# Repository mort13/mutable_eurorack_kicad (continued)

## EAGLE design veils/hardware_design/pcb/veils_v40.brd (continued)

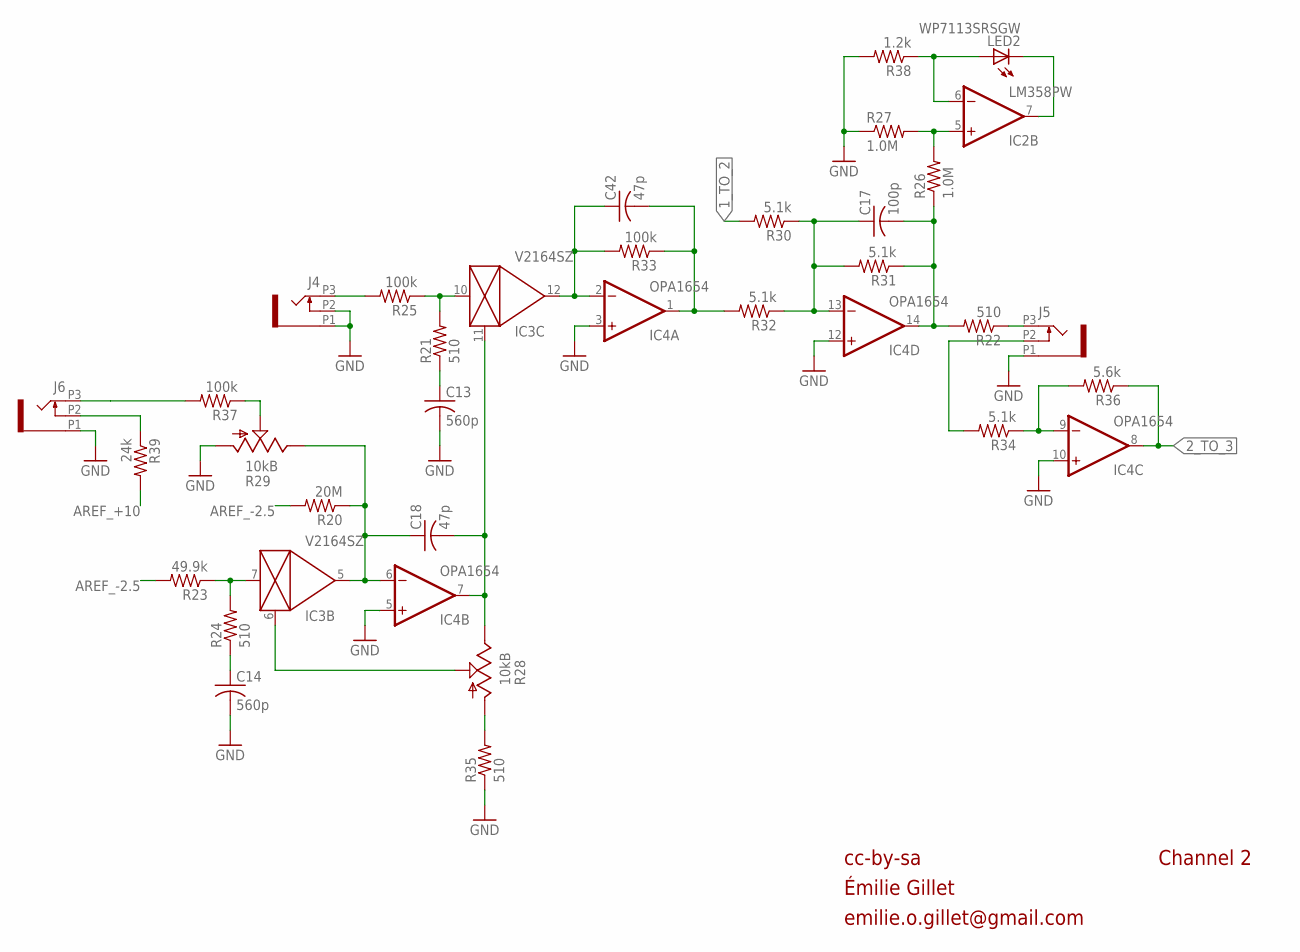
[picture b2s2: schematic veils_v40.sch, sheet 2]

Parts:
C13, C14: 560p; C0402
C17: 100p; C0402
C18, C42: 47p; C0402
IC2: LM358PW; TSSOP8
IC3: V2164SZ; SOIC16N
IC4: OPA1654; TSSOP14
J4, J5, J6: PJ301_THONKICONN6; WQP_PJ_301M6
LED2: WP7113SRSGW; LED5MM
R20: 20M; R0402
R21, R22, R24, R35: 510; R0402
R23: 49.9k; R0402
R25, R33, R37: 100k; R0402
R26, R27: 1.0M; R0402
R28: 10kB; ALPS_POT_VERTICAL
R29: 10kB; ALPS_POT_VERTICAL_PS
R30, R31, R32, R34: 5.1k; R0402
R36: 5.6k; R0402
R38: 1.2k; R0402
R39: 24k; R0402

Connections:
1_TO_2: R30.2; also elsewhere on the board
2_TO_3: IC4.8 (OUT), R36.1; also elsewhere on the board
AREF_+10: R39.2; also elsewhere on the board
AREF_-2.5: R20.2, R23.2; also elsewhere on the board
FOO1: IC3.7 (IN), R23.1, R24.2
GND: C13.2, C14.2, IC4.3 (+IN), IC4.5 (+IN), IC4.10 (+IN), IC4.12 (+IN), J4.P1 (1), J4.P2 (2), J5.P1 (1), J6.P1 (1), R27.1, R29.P$3 (A), R35.1, R38.2; also elsewhere on the board
unnamed: J4.P3 (3), R25.2
unnamed: IC2.5 (+IN), R26.2, R27.2
unnamed: J5.P3 (3), R22.1
unnamed: C13.1, R21.1
unnamed: IC3.10 (IN), R21.2, R25.1
unnamed: IC3.6 (CTRL), R28.P$2 (S)
unnamed: C17.1, IC4.13 (-IN), R30.1, R31.2, R32.1
unnamed: C18.2, IC3.11 (CTRL), IC4.7 (OUT), R28.P$1 (E)
unnamed: R28.P$3 (A), R35.2
unnamed: IC2.7 (OUT), LED2.K (C)
unnamed: IC2.6 (-IN), LED2.A, R38.1
unnamed: IC4.9 (-IN), R34.1, R36.2
unnamed: J5.P2 (2), R34.2
unnamed: C42.2, IC4.1 (OUT), R32.2, R33.1
unnamed: R29.P$2 (S), R37.1
unnamed: C14.1, R24.1
unnamed: C18.1, IC3.5 (OUT), IC4.6 (-IN), R20.1, R29.P$1 (E)
unnamed: J6.P3 (3), R37.2
unnamed: C42.1, IC3.12 (OUT), IC4.2 (-IN), R33.2
unnamed: J6.P2 (2), R39.1
OUT2: C17.2, IC4.14 (OUT), R22.2, R26.1, R31.1

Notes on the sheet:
cc-by-sa
Channel 2
Émilie Gillet
emilie.o.gillet@gmail.com

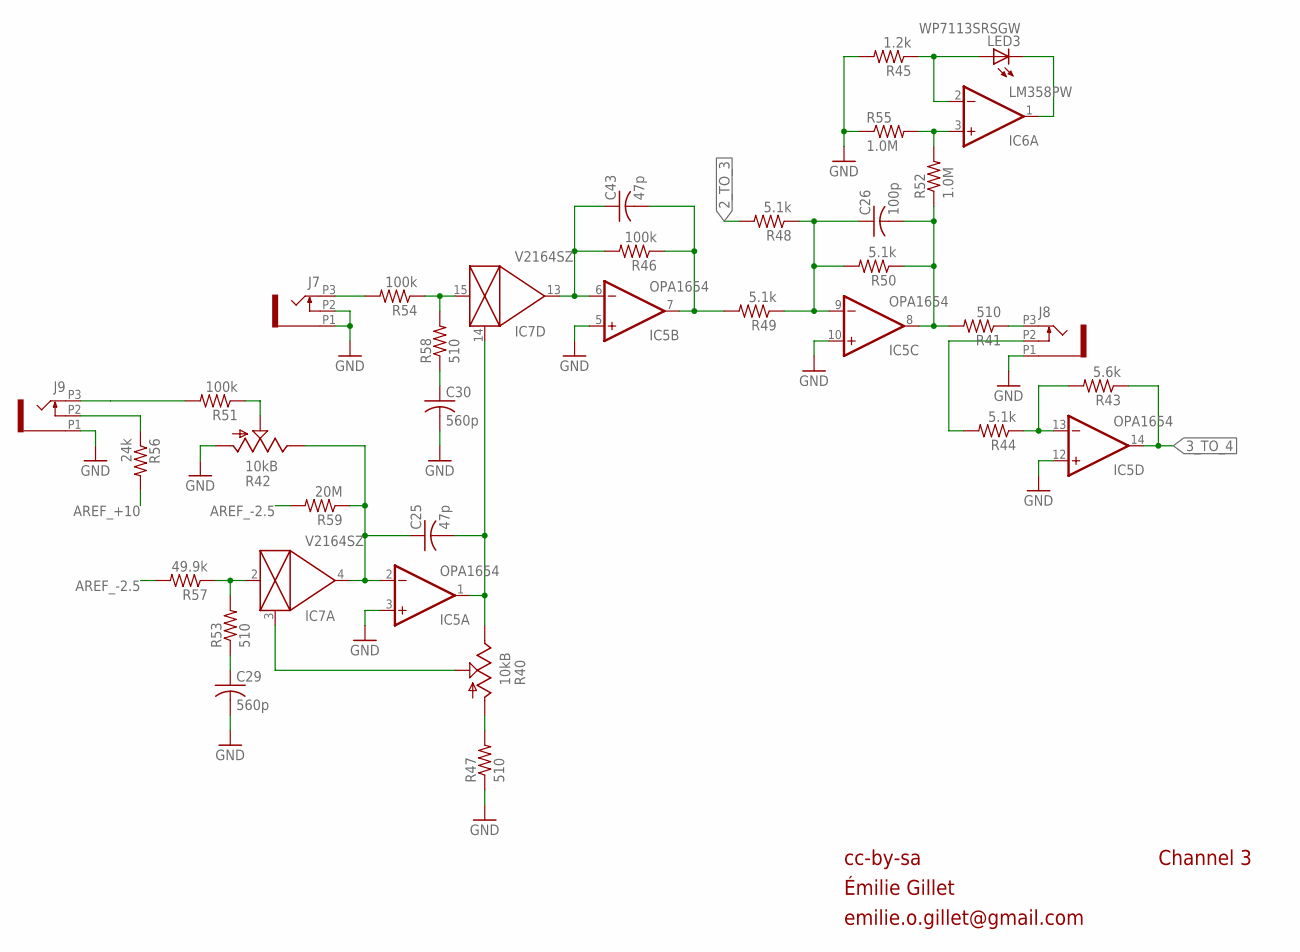
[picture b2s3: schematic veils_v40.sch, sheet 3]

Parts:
C25, C43: 47p; C0402
C26: 100p; C0402
C29, C30: 560p; C0402
IC5: OPA1654; TSSOP14
IC6: LM358PW; TSSOP8
IC7: V2164SZ; SOIC16N
J7, J8, J9: PJ301_THONKICONN6; WQP_PJ_301M6
LED3: WP7113SRSGW; LED5MM
R40: 10kB; ALPS_POT_VERTICAL
R41, R47, R53, R58: 510; R0402
R42: 10kB; ALPS_POT_VERTICAL_PS
R43: 5.6k; R0402
R44, R48, R49, R50: 5.1k; R0402
R45: 1.2k; R0402
R46, R51, R54: 100k; R0402
R52, R55: 1.0M; R0402
R56: 24k; R0402
R57: 49.9k; R0402
R59: 20M; R0402

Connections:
2_TO_3: R48.2; also elsewhere on the board
3_TO_4: IC5.14 (OUT), R43.1; also elsewhere on the board
AREF_+10: R56.2; also elsewhere on the board
AREF_-2.5: R57.2, R59.2; also elsewhere on the board
FOO2: IC7.2 (IN), R53.2, R57.1
GND: C29.2, C30.2, IC5.3 (+IN), IC5.5 (+IN), IC5.10 (+IN), IC5.12 (+IN), J7.P1 (1), J7.P2 (2), J8.P1 (1), J9.P1 (1), R42.P$3 (A), R45.2, R47.1, R55.1; also elsewhere on the board
unnamed: IC6.3 (+IN), R52.2, R55.2
unnamed: J8.P3 (3), R41.1
unnamed: IC7.3 (CTRL), R40.P$2 (S)
unnamed: C25.2, IC5.1 (OUT), IC7.14 (CTRL), R40.P$1 (E)
unnamed: R40.P$3 (A), R47.2
unnamed: C30.1, R58.1
unnamed: IC7.15 (IN), R54.1, R58.2
unnamed: C26.1, IC5.9 (-IN), R48.1, R49.1, R50.2
unnamed: J9.P2 (2), R56.1
unnamed: J7.P3 (3), R54.2
unnamed: J9.P3 (3), R51.2
unnamed: C43.1, IC5.6 (-IN), IC7.13 (OUT), R46.2
unnamed: IC6.1 (OUT), LED3.K (C)
unnamed: IC6.2 (-IN), LED3.A, R45.1
unnamed: IC5.13 (-IN), R43.2, R44.1
unnamed: J8.P2 (2), R44.2
unnamed: C29.1, R53.1
unnamed: C25.1, IC5.2 (-IN), IC7.4 (OUT), R42.P$1 (E), R59.1
unnamed: R42.P$2 (S), R51.1
unnamed: C43.2, IC5.7 (OUT), R46.1, R49.2
OUT3: C26.2, IC5.8 (OUT), R41.2, R50.1, R52.1

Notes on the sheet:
cc-by-sa
Channel 3
Émilie Gillet
emilie.o.gillet@gmail.com

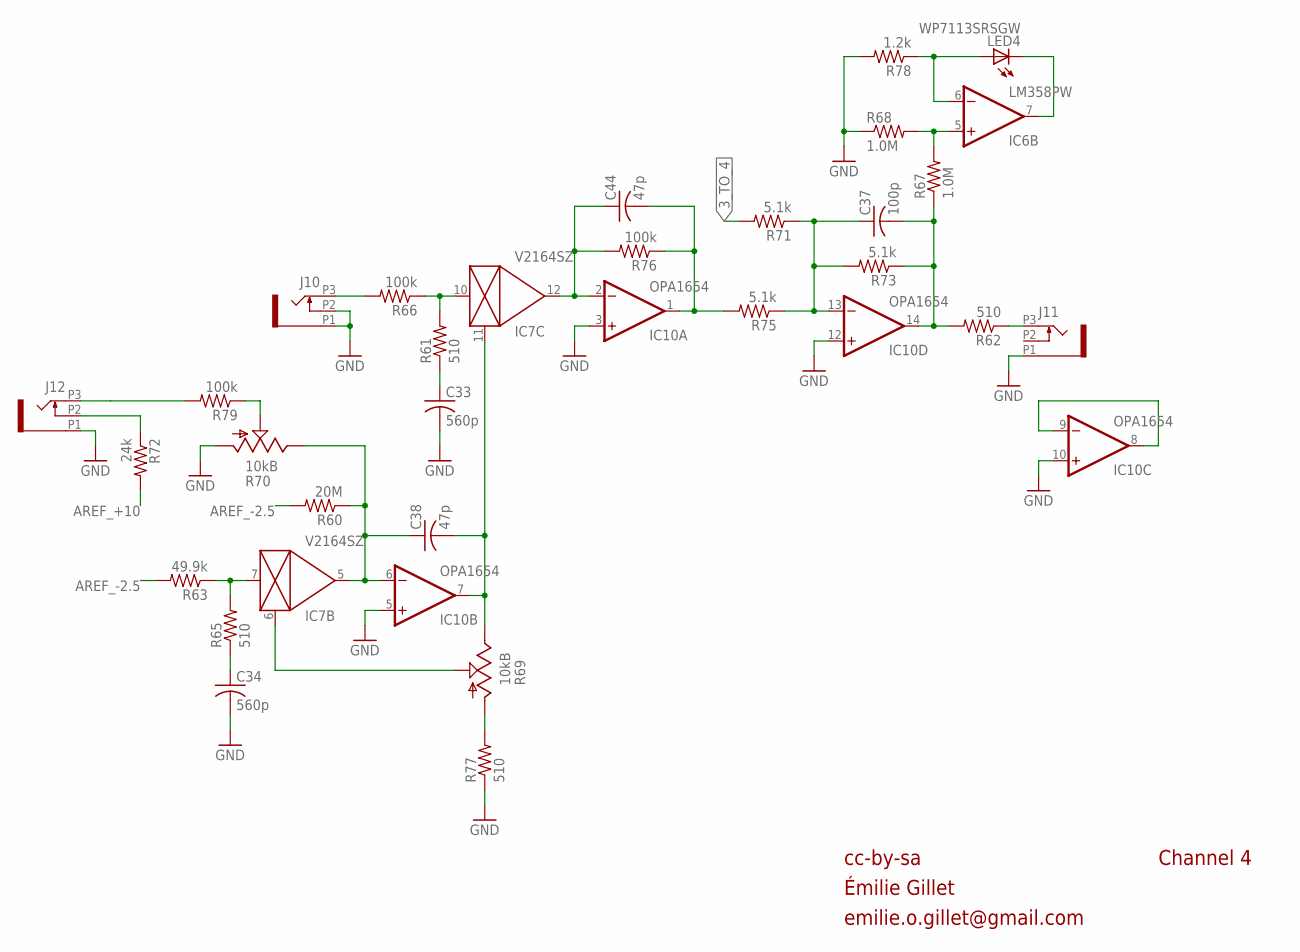
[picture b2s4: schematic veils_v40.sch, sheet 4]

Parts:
C33, C34: 560p; C0402
C37: 100p; C0402
C38, C44: 47p; C0402
IC6: LM358PW; TSSOP8
IC7: V2164SZ; SOIC16N
IC10: OPA1654; TSSOP14
J10, J11, J12: PJ301_THONKICONN6; WQP_PJ_301M6
LED4: WP7113SRSGW; LED5MM
R60: 20M; R0402
R61, R62, R65, R77: 510; R0402
R63: 49.9k; R0402
R66, R76, R79: 100k; R0402
R67, R68: 1.0M; R0402
R69: 10kB; ALPS_POT_VERTICAL
R70: 10kB; ALPS_POT_VERTICAL_PS
R71, R73, R75: 5.1k; R0402
R72: 24k; R0402
R78: 1.2k; R0402

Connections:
3_TO_4: R71.2; also elsewhere on the board
AREF_+10: R72.2; also elsewhere on the board
AREF_-2.5: R60.2, R63.2; also elsewhere on the board
FOO3: IC7.7 (IN), R63.1, R65.2
GND: C33.2, C34.2, IC10.3 (+IN), IC10.5 (+IN), IC10.10 (+IN), IC10.12 (+IN), J10.P1 (1), J10.P2 (2), J11.P1 (1), J12.P1 (1), R68.1, R70.P$3 (A), R77.1, R78.2; also elsewhere on the board
unnamed: IC10.8 (OUT), IC10.9 (-IN)
unnamed: IC6.5 (+IN), R67.2, R68.2
unnamed: C38.2, IC7.11 (CTRL), IC10.7 (OUT), R69.P$1 (E)
unnamed: IC7.6 (CTRL), R69.P$2 (S)
unnamed: R69.P$3 (A), R77.2
unnamed: C44.1, IC7.12 (OUT), IC10.2 (-IN), R76.2
unnamed: J10.P3 (3), R66.2
unnamed: J11.P3 (3), R62.1
unnamed: C33.1, R61.1
unnamed: IC7.10 (IN), R61.2, R66.1
unnamed: C37.1, IC10.13 (-IN), R71.1, R73.2, R75.1
unnamed: J12.P3 (3), R79.2
unnamed: IC6.7 (OUT), LED4.K (C)
unnamed: IC6.6 (-IN), LED4.A, R78.1
unnamed: C44.2, IC10.1 (OUT), R75.2, R76.1
unnamed: R70.P$2 (S), R79.1
unnamed: C34.1, R65.1
unnamed: C38.1, IC7.5 (OUT), IC10.6 (-IN), R60.1, R70.P$1 (E)
unnamed: J12.P2 (2), R72.1
OUT4: C37.2, IC10.14 (OUT), R62.2, R67.1, R73.1

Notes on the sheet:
cc-by-sa
Channel 4
Émilie Gillet
emilie.o.gillet@gmail.com

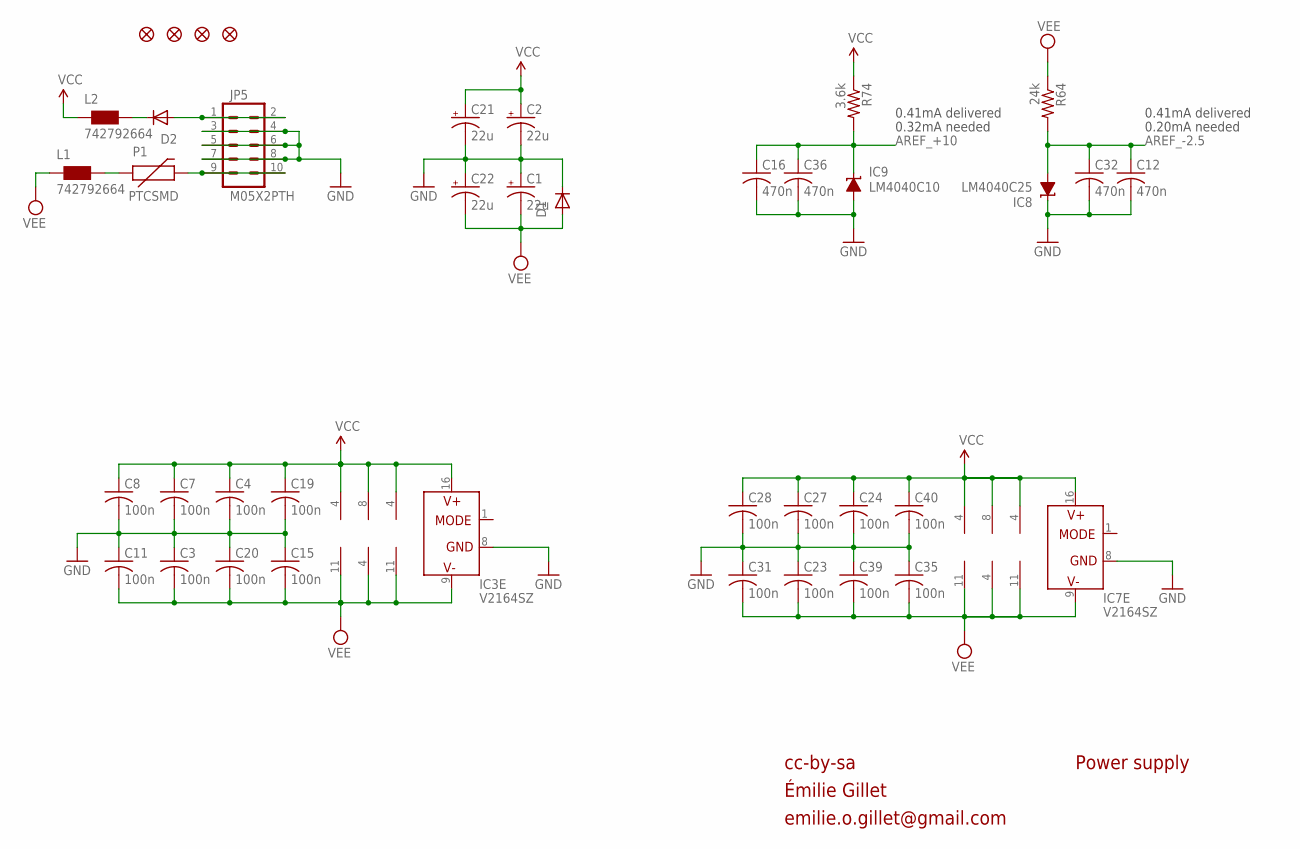
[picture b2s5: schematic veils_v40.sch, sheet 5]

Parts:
C1, C2, C21, C22: 22u; PANASONIC_B
C3, C4, C7, C8, C11, C15, C19, C20, C23, C24, C27, C28, C31, C35, C39, C40: 100n; C0402
C12, C16, C32, C36: 470n; C0402
D1, D2: 1N5819HW; SOD123
IC1, IC4, IC5, IC10: OPA1654; TSSOP14
IC2, IC6: LM358PW; TSSOP8
IC3, IC7: V2164SZ; SOIC16N
IC8: LM4040C25; DBZ_R-PDSO-G3
IC9: LM4040C10; DBZ_R-PDSO-G3
JP1, JP2, JP3, JP4: FIDUCIAL1X2; FIDUCIAL-1X2
JP5: M05X2PTH; AVR_ICSP
L1, L2: 742792664; 0603
P1: PTCSMD; PTC-1206
R64: 24k; R0402
R74: 3.6k; R0402

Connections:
AREF_+10: C16.1, C36.1, IC9.1 (C), R74.2; also elsewhere on the board
AREF_-2.5: C12.1, C32.1, IC8.2 (A), R64.2; also elsewhere on the board
GND: C1.+, C2.-, C3.1, C4.2, C7.2, C8.2, C11.1, C12.2, C15.1, C16.2, C19.2, C20.1, C21.-, C22.+, C23.1, C24.2, C27.2, C28.2, C31.1, C32.2, C35.1, C36.2, C39.1, C40.2, D1.C, IC3.8 (GND), IC7.8 (GND), IC8.1 (C), IC9.2 (A), JP5.3, JP5.4, JP5.5, JP5.6, JP5.7, JP5.8; also elsewhere on the board
unnamed: D2.A, JP5.1, JP5.2
unnamed: JP5.9, JP5.10, P1.2
unnamed: L1.2, P1.1
unnamed: D2.C, L2.2
VCC: C2.+, C4.1, C7.1, C8.1, C19.1, C21.+, C24.1, C27.1, C28.1, C40.1, IC1.4 (V+), IC2.8 (V+), IC3.16 (V+), IC4.4 (V+), IC5.4 (V+), IC6.8 (V+), IC7.16 (V+), IC10.4 (V+), L2.1, R74.1
VEE: C1.-, C3.2, C11.2, C15.2, C20.2, C22.-, C23.2, C31.2, C35.2, C39.2, D1.A, IC1.11 (V-), IC2.4 (V-), IC3.9 (V-), IC4.11 (V-), IC5.11 (V-), IC6.4 (V-), IC7.9 (V-), IC10.11 (V-), L1.1, R64.1

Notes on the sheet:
cc-by-sa
Power supply
0.41mA delivered
0.20mA needed
0.32mA needed
Émilie Gillet
emilie.o.gillet@gmail.com

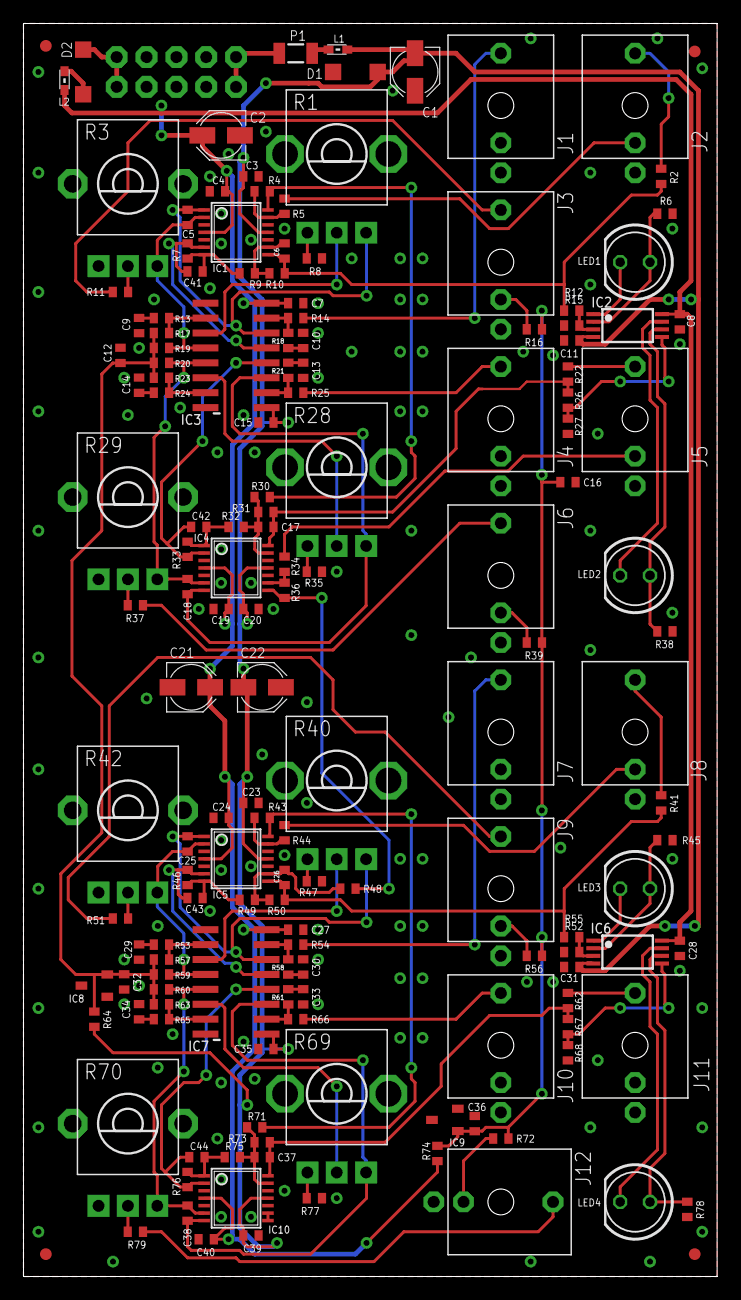
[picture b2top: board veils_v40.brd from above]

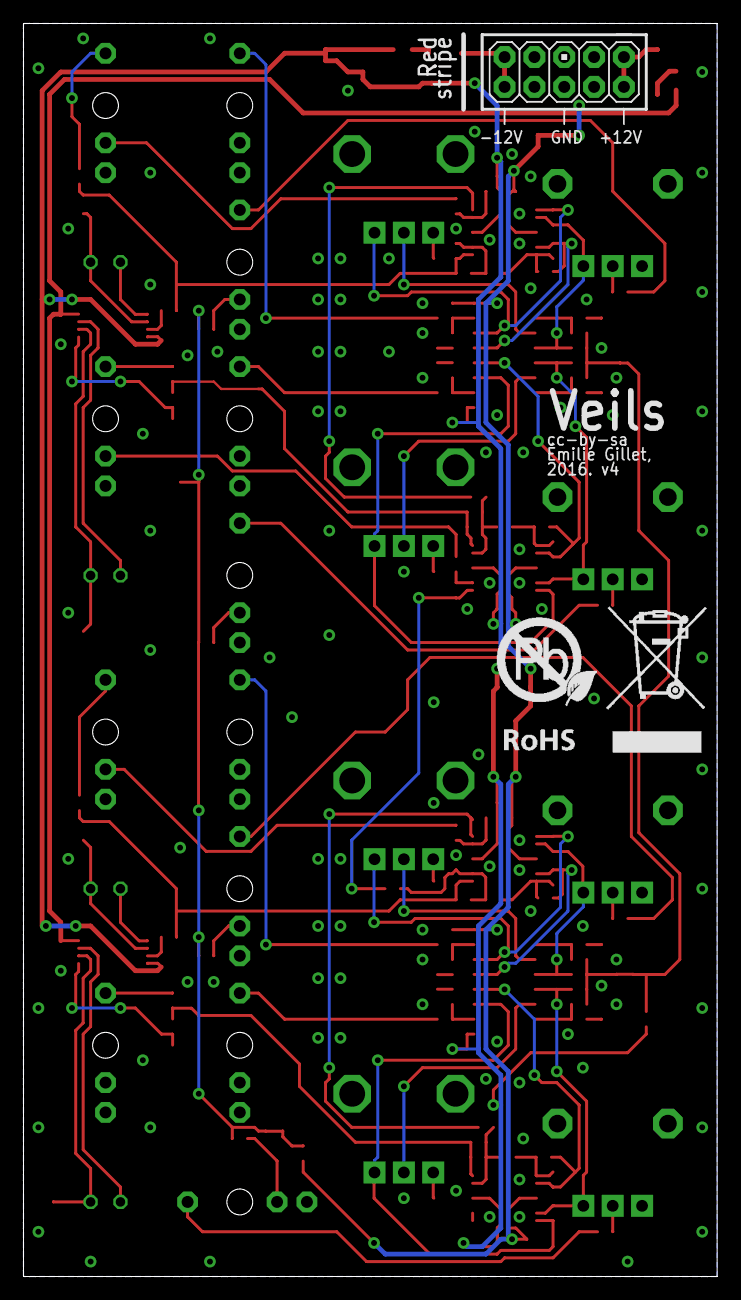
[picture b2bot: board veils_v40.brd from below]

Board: 2 copper layers, 59.1 x 106.7 mm, 160 parts (2 on the bottom side), 99 nets.

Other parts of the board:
U$2: ROHS_BIG

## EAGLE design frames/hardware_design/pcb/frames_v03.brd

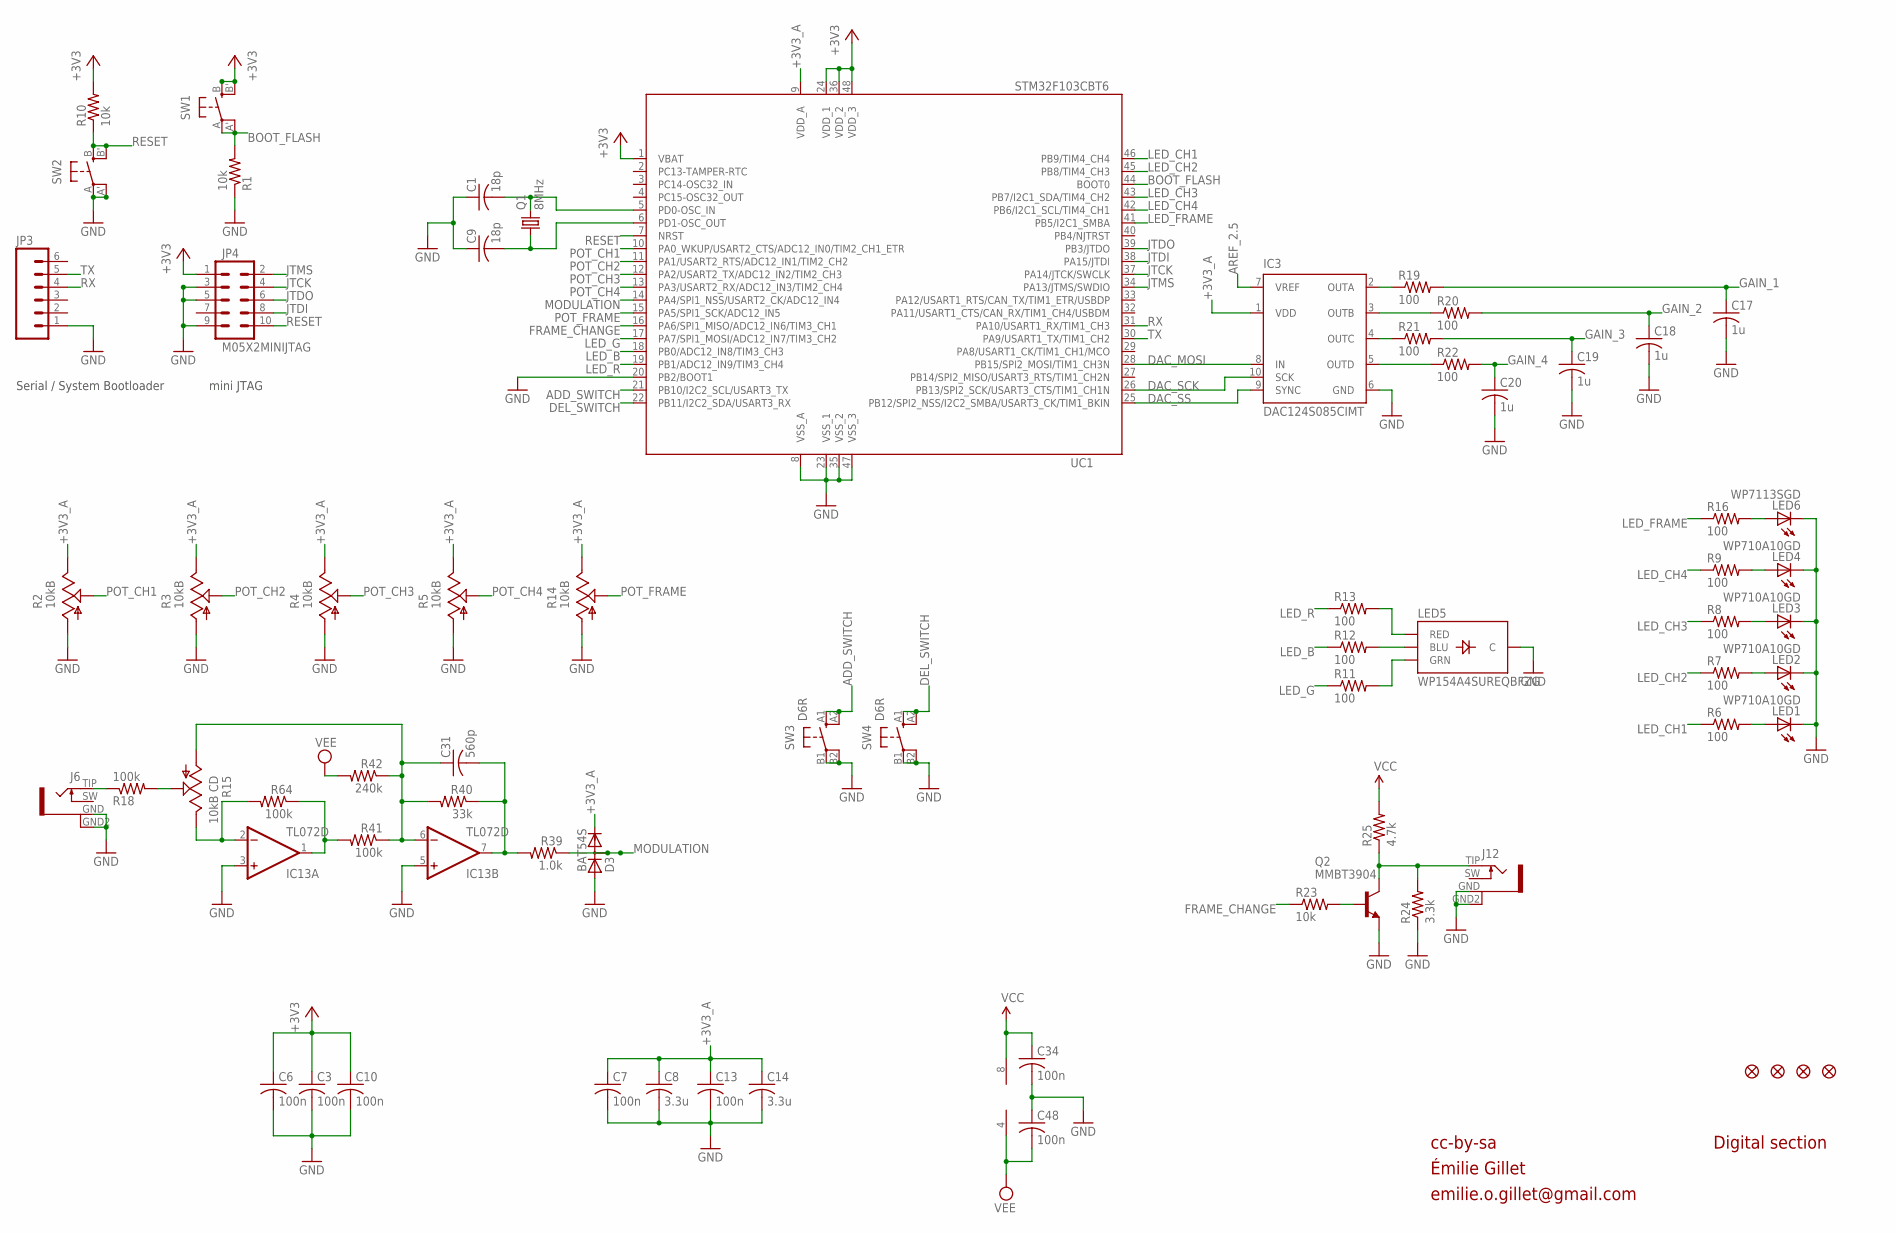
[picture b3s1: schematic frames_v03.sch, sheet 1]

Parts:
C1, C9: 18p; C0603
C3, C6, C7, C10, C13, C34, C48: 100n; C0603
C8, C14: 3.3u; C0603
C17, C18, C19, C20: 1u; C0603
C31: 560p; C0603
D3: BAT54S; SOT23
F1, F2, F3, F4: FIDUCIAL1X2; FIDUCIAL-1X2
IC3: DAC124S085CIMT; MSOP10
IC13: TL072D; SO08
J6, J12: PJ301WQP; WQP_PJ_301BM
JP3: M06SIP; 1X06
JP4: M05X2MINIJTAG; 2X5-1.27
LED1, LED2, LED3, LED4: WP710A10GD; LED3MM
LED5: WP154A4SUREQBFZG; LED-TRICOLOR-THROUGHHOLE
LED6: WP7113SGD; LED5MM
Q1: 8MHz; HC49UP
Q2: MMBT3904; SOT23-BEC
R1, R10, R23: 10k; R0603
R2, R3, R4, R5, R14: 10kB; ALPS_POT_VERTICAL_PS
R6, R7, R8, R9, R11, R12, R13, R16, R19, R20, R21, R22: 100; R0603
R15: 10kB CD; ALPS_POT_VERTICAL_PS
R18, R41, R64: 100k; R0603
R24: 3.3k; R0603
R25: 4.7k; R0603
R39: 1.0k; R0603
R40: 33k; R0603
R42: 240k; R0603
SW1, SW2: EVQQ2; EVQ-Q2
SW3, SW4: D6R
UC1: STM32F103CBT6; LQFP48

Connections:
+3V3: C3.1, C6.1, C10.1, JP4.1, R10.2, SW1.B (S), SW1.B' (S1), UC1.1 (VBAT), UC1.24 (VDD_1), UC1.36 (VDD_2), UC1.48 (VDD_3); also elsewhere on the board
+3V3_A: C7.1, C8.1, C13.1, C14.1, D3.2 (C), IC3.1 (VDD), R2.P$1 (E), R3.P$1 (E), R4.P$1 (E), R5.P$1 (E), R14.P$1 (E), UC1.9 (VDD_A); also elsewhere on the board
ADD_SWITCH: SW3.A1 (S), SW3.A2 (S1), UC1.21 (PB10/I2C2_SCL/USART3_TX)
AREF_2.5: IC3.7 (VREF); also elsewhere on the board
BOOT_FLASH: R1.2, SW1.A, SW1.A' (P1), UC1.44 (BOOT0)
DAC_MOSI: IC3.8 (IN), UC1.28 (PB15/SPI2_MOSI/TIM1_CH3N)
DAC_SCK: IC3.10 (SCK), UC1.26 (PB13/SPI2_SCK/USART3_CTS/TIM1_CH1N)
DAC_SS: IC3.9 (SYNC), UC1.25 (PB12/SPI2_NSS/I2C2_SMBA/USART3_CK/TIM1_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)
DEL_SWITCH: SW4.A1 (S), SW4.A2 (S1), UC1.22 (PB11/I2C2_SDA/USART3_RX)
FRAME_CHANGE: R23.1, UC1.16 (PA6/SPI1_MISO/ADC12_IN6/TIM3_CH1)
GAIN_1: C17.1, R19.2; also elsewhere on the board
GAIN_2: C18.1, R20.2; also elsewhere on the board
GAIN_3: C19.1, R21.2; also elsewhere on the board
GAIN_4: C20.1, R22.2; also elsewhere on the board
GATE2_LED: LED3.A, R8.2
GATE3_LED: LED2.A, R7.2
GATE4_LED: LED1.A, R6.2
GND: C1.1, C3.2, C6.2, C7.2, C8.2, C9.1, C10.2, C13.2, C14.2, C17.2, C18.2, C19.2, C20.2, C34.2, C48.1, D3.1 (A), IC3.6 (GND), IC13.3 (+IN), IC13.5 (+IN), J6.GND (1), J6.GND2 (4), J12.GND (1), J12.GND2 (4), JP3.1, JP4.3, JP4.5, JP4.9, LED1.K (C), LED2.K (C), LED3.K (C), LED4.K (C), LED5.GND (C), LED6.K (C), Q2.E, R1.1, R2.P$3 (A), R3.P$3 (A), R4.P$3 (A), R5.P$3 (A), R14.P$3 (A), R24.1, SW2.A, SW2.A' (P1), SW3.B1, SW3.B2 (P1), SW4.B1, SW4.B2 (P1), UC1.8 (VSS_A), UC1.20 (PB2/BOOT1), UC1.23 (VSS_1), UC1.35 (VSS_2), UC1.47 (VSS_3); also elsewhere on the board
JTCK: JP4.4, UC1.37 (PA14/JTCK/SWCLK)
JTDI: JP4.8, UC1.38 (PA15/JTDI)
JTDO: JP4.6, UC1.39 (PB3/JTDO)
JTMS: JP4.2, UC1.34 (PA13/JTMS/SWDIO)
LED_B: R12.1, UC1.18 (PB0/ADC12_IN8/TIM3_CH3)
LED_CH1: R6.1, UC1.46 (PB9/TIM4_CH4)
LED_CH2: R7.1, UC1.45 (PB8/TIM4_CH3)
LED_CH3: R8.1, UC1.43 (PB7/I2C1_SDA/TIM4_CH2)
LED_CH4: R9.1, UC1.42 (PB6/I2C1_SCL/TIM4_CH1)
LED_FRAME: R16.1, UC1.41 (PB5/I2C1_SMBA)
LED_G: R11.1, UC1.17 (PA7/SPI1_MOSI/ADC12_IN7/TIM3_CH2)
LED_R: R13.1, UC1.19 (PB1/ADC12_IN9/TIM3_CH4)
MODULATION: D3.3 (AC), R39.1, UC1.14 (PA4/SPI1_NSS/USART2_CK/ADC12_IN4)
unnamed: IC13.2 (-IN), R15.P$1 (E), R64.2
unnamed: R15.P$2 (S), R18.2
unnamed: LED4.A, R9.2
unnamed: C1.2, Q1.2, UC1.5 (PD0-OSC_IN)
unnamed: C9.2, Q1.1, UC1.6 (PD1-OSC_OUT)
unnamed: IC13.1 (OUT), R41.2, R64.1
unnamed: J6.TIP (2), R18.1
unnamed: C31.2, IC13.7 (OUT), R39.2, R40.1
unnamed: C31.1, IC13.6 (-IN), R15.P$3 (A), R40.2, R41.1, R42.1
unnamed: LED6.A, R16.2
unnamed: LED5.RED, R13.2
unnamed: LED5.BLU, R12.2
unnamed: LED5.GRN, R11.2
unnamed: IC3.2 (OUTA), R19.1
unnamed: IC3.3 (OUTB), R20.1
unnamed: IC3.4 (OUTC), R21.1
unnamed: J12.TIP (2), Q2.C, R24.2, R25.1
unnamed: IC3.5 (OUTD), R22.1
unnamed: Q2.B, R23.2
POT_CH1: R2.P$2 (S), UC1.10 (PA0_WKUP/USART2_CTS/ADC12_IN0/TIM2_CH1_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)
POT_CH2: R3.P$2 (S), UC1.11 (PA1/USART2_RTS/ADC12_IN1/TIM2_CH2)
POT_CH3: R4.P$2 (S), UC1.12 (PA2/USART2_TX/ADC12_IN2/TIM2_CH3)
POT_CH4: R5.P$2 (S), UC1.13 (PA3/USART2_RX/ADC12_IN3/TIM2_CH4)
POT_FRAME: R14.P$2 (S), UC1.15 (PA5/SPI1_SCK/ADC12_IN5)
RESET: JP4.10, R10.1, SW2.B (S), SW2.B' (S1), UC1.7 (NRST)
RX: JP3.4, UC1.31 (PA10/USART1_RX/TIM1_CH3)
TX: JP3.5, UC1.30 (PA9/USART1_TX/TIM1_CH2)
VCC: C34.1, IC13.8 (V+), R25.2; also elsewhere on the board
VEE: C48.2, IC13.4 (V-), R42.2; also elsewhere on the board

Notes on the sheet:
cc-by-sa
Serial / System Bootloader
mini JTAG
Digital section
Émilie Gillet
emilie.o.gillet@gmail.com

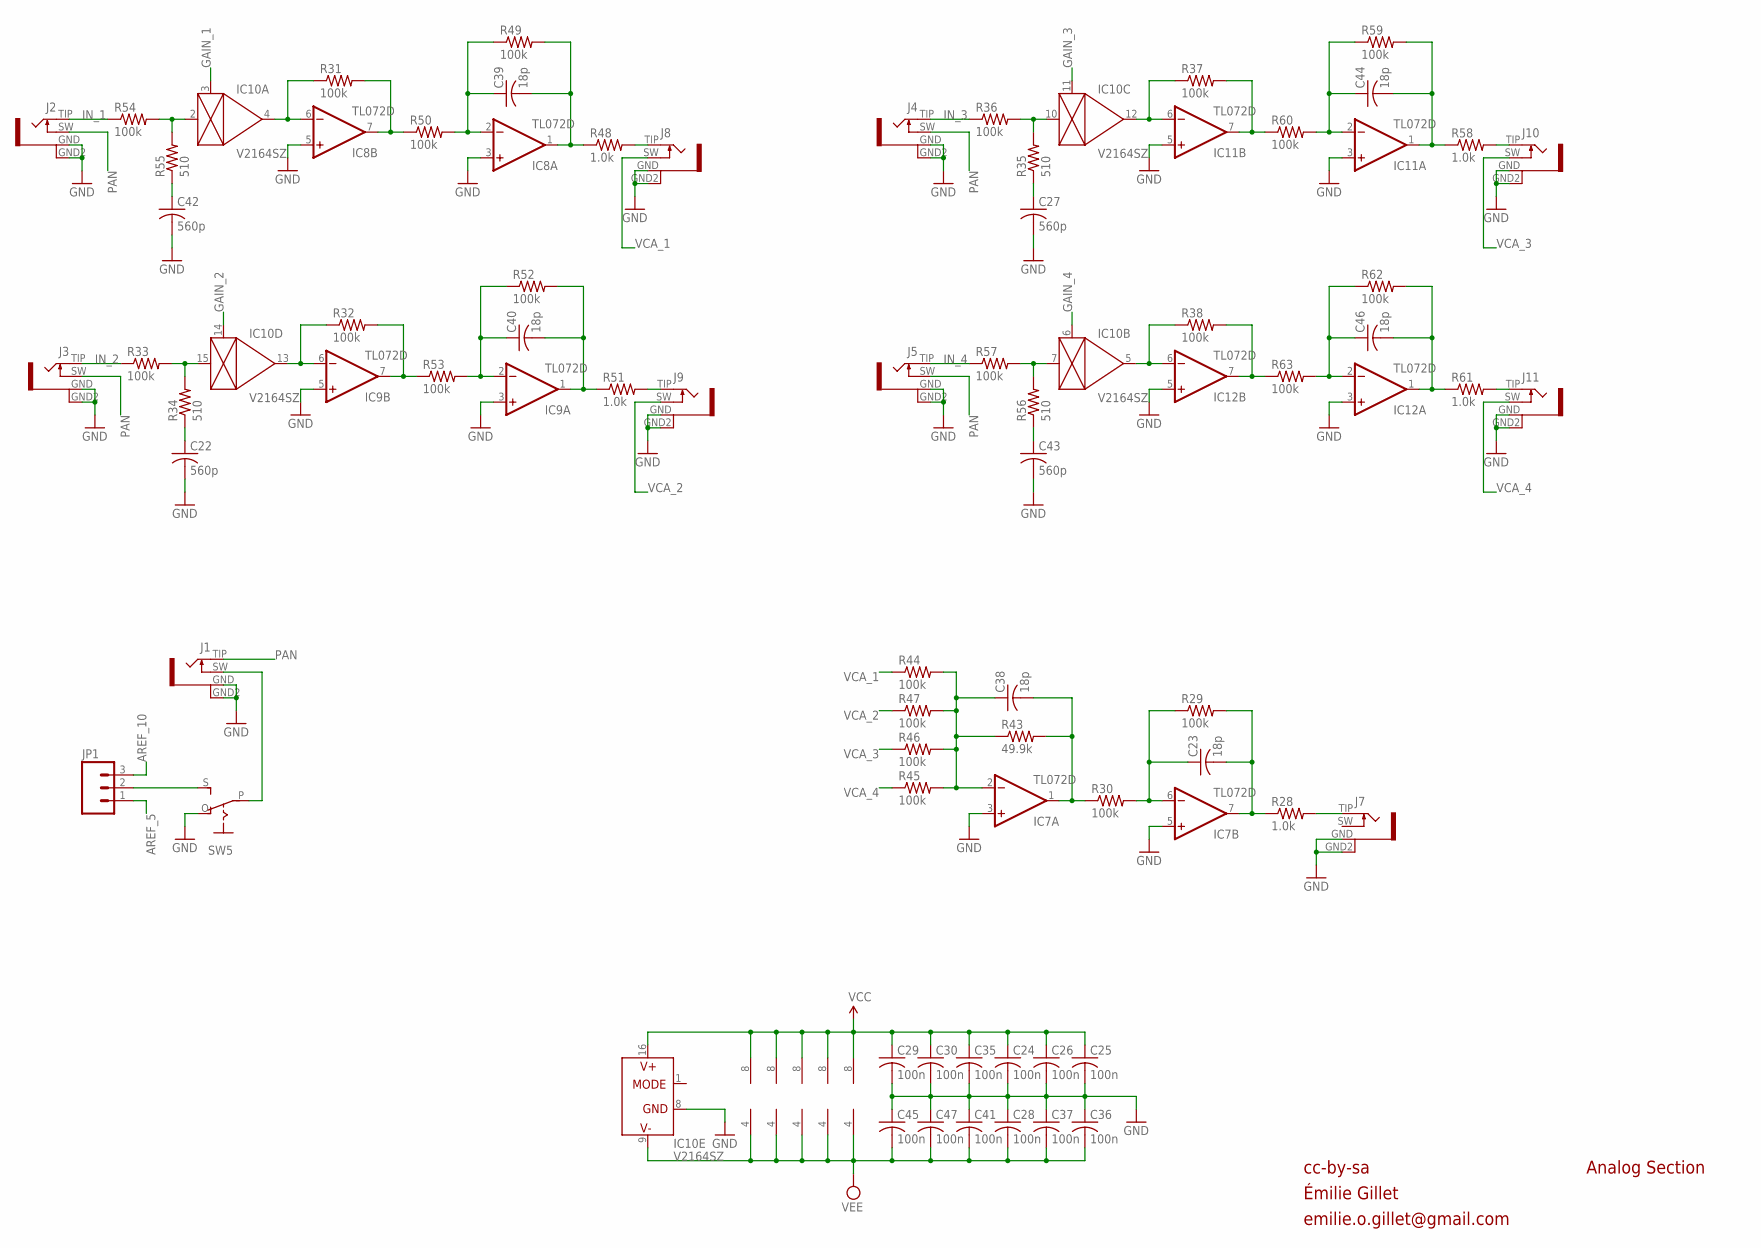
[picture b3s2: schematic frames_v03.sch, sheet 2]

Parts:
C22, C27, C42, C43: 560p; C0603
C23, C38, C39, C40, C44, C46: 18p; C0603
C24, C25, C26, C28, C29, C30, C35, C36, C37, C41, C45, C47: 100n; C0603
IC7, IC8, IC9, IC11, IC12: TL072D; SO08
IC10: V2164SZ; SOIC16N
J1, J2, J3, J4, J5, J7, J8, J9, J10, J11: PJ301WQP; WQP_PJ_301BM
JP1: M03PTH; 1X03
R28, R48, R51, R58, R61: 1.0k; R0603
R29, R30, R31, R32, R33, R36, R37, R38, R44, R45, R46, R47, R49, R50, R52, R53, R54, R57, R59, R60, R62, R63: 100k; R0603
R34, R35, R55, R56: 510; R0603
R43: 49.9k; R0603
SW5: S-ON-ONSMALL_SLIDE; ES_100SP1T6B11M2QEH_SMALL

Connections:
AREF_5: JP1.1; also elsewhere on the board
AREF_10: JP1.3; also elsewhere on the board
FB_CURRENT: IC10.2 (IN), R54.2, R55.2
FB_CURRENT1: IC10.15 (IN), R33.2, R34.2
FB_CURRENT2: IC10.10 (IN), R35.2, R36.2
FB_CURRENT3: IC10.7 (IN), R56.2, R57.2
GAIN_1: IC10.3 (CTRL); also elsewhere on the board
GAIN_2: IC10.14 (CTRL); also elsewhere on the board
GAIN_3: IC10.11 (CTRL); also elsewhere on the board
GAIN_4: IC10.6 (CTRL); also elsewhere on the board
GND: C22.2, C24.2, C25.2, C26.2, C27.2, C28.1, C29.2, C30.2, C35.2, C36.1, C37.1, C41.1, C42.2, C43.2, C45.1, C47.1, IC7.3 (+IN), IC7.5 (+IN), IC8.3 (+IN), IC8.5 (+IN), IC9.3 (+IN), IC9.5 (+IN), IC10.8 (GND), IC11.3 (+IN), IC11.5 (+IN), IC12.3 (+IN), IC12.5 (+IN), J1.GND (1), J1.GND2 (4), J2.GND (1), J2.GND2 (4), J3.GND (1), J3.GND2 (4), J4.GND (1), J4.GND2 (4), J5.GND (1), J5.GND2 (4), J7.GND (1), J7.GND2 (4), J8.GND (1), J8.GND2 (4), J9.GND (1), J9.GND2 (4), J10.GND (1), J10.GND2 (4), J11.GND (1), J11.GND2 (4), SW5.O; also elsewhere on the board
IN_1: J2.TIP (2), R54.1
IN_2: J3.TIP (2), R33.1
IN_3: J4.TIP (2), R36.1
IN_4: J5.TIP (2), R57.1
unnamed: C42.1, R55.1
unnamed: J7.TIP (2), R28.2
unnamed: IC9.7 (OUT), R32.2, R53.1
unnamed: C27.1, R35.1
unnamed: IC8.6 (-IN), IC10.4 (OUT), R31.1
unnamed: C39.1, IC8.2 (-IN), R49.1, R50.2
unnamed: C39.2, IC8.1 (OUT), R48.1, R49.2
unnamed: C23.2, IC7.7 (OUT), R28.1, R29.2
unnamed: C22.1, R34.1
unnamed: C38.1, IC7.2 (-IN), R43.1, R44.2, R45.2, R46.2, R47.2
unnamed: IC9.6 (-IN), IC10.13 (OUT), R32.1
unnamed: C23.1, IC7.6 (-IN), R29.1, R30.2
unnamed: C40.1, IC9.2 (-IN), R52.1, R53.2
unnamed: C40.2, IC9.1 (OUT), R51.1, R52.2
unnamed: IC10.12 (OUT), IC11.6 (-IN), R37.1
unnamed: C44.1, IC11.2 (-IN), R59.1, R60.2
unnamed: C44.2, IC11.1 (OUT), R58.1, R59.2
unnamed: C43.1, R56.1
unnamed: C38.2, IC7.1 (OUT), R30.1, R43.2
unnamed: IC10.5 (OUT), IC12.6 (-IN), R38.1
unnamed: C46.1, IC12.2 (-IN), R62.1, R63.2
unnamed: C46.2, IC12.1 (OUT), R61.1, R62.2
unnamed: J1.SW (3), SW5.P
unnamed: J8.TIP (2), R48.2
unnamed: JP1.2, SW5.S
unnamed: IC12.7 (OUT), R38.2, R63.1
unnamed: J9.TIP (2), R51.2
unnamed: J11.TIP (2), R61.2
unnamed: J10.TIP (2), R58.2
PAN: J1.TIP (2), J2.SW (3), J3.SW (3), J4.SW (3), J5.SW (3)
VCA0_1: IC8.7 (OUT), R31.2, R50.1
VCA0_3: IC11.7 (OUT), R37.2, R60.1
VCA_1: J8.SW (3), R44.1
VCA_2: J9.SW (3), R47.1
VCA_3: J10.SW (3), R46.1
VCA_4: J11.SW (3), R45.1
VCC: C24.1, C25.1, C26.1, C29.1, C30.1, C35.1, IC7.8 (V+), IC8.8 (V+), IC9.8 (V+), IC10.16 (V+), IC11.8 (V+), IC12.8 (V+); also elsewhere on the board
VEE: C28.2, C36.2, C37.2, C41.2, C45.2, C47.2, IC7.4 (V-), IC8.4 (V-), IC9.4 (V-), IC10.9 (V-), IC11.4 (V-), IC12.4 (V-); also elsewhere on the board

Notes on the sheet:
cc-by-sa
Analog Section
Émilie Gillet
emilie.o.gillet@gmail.com

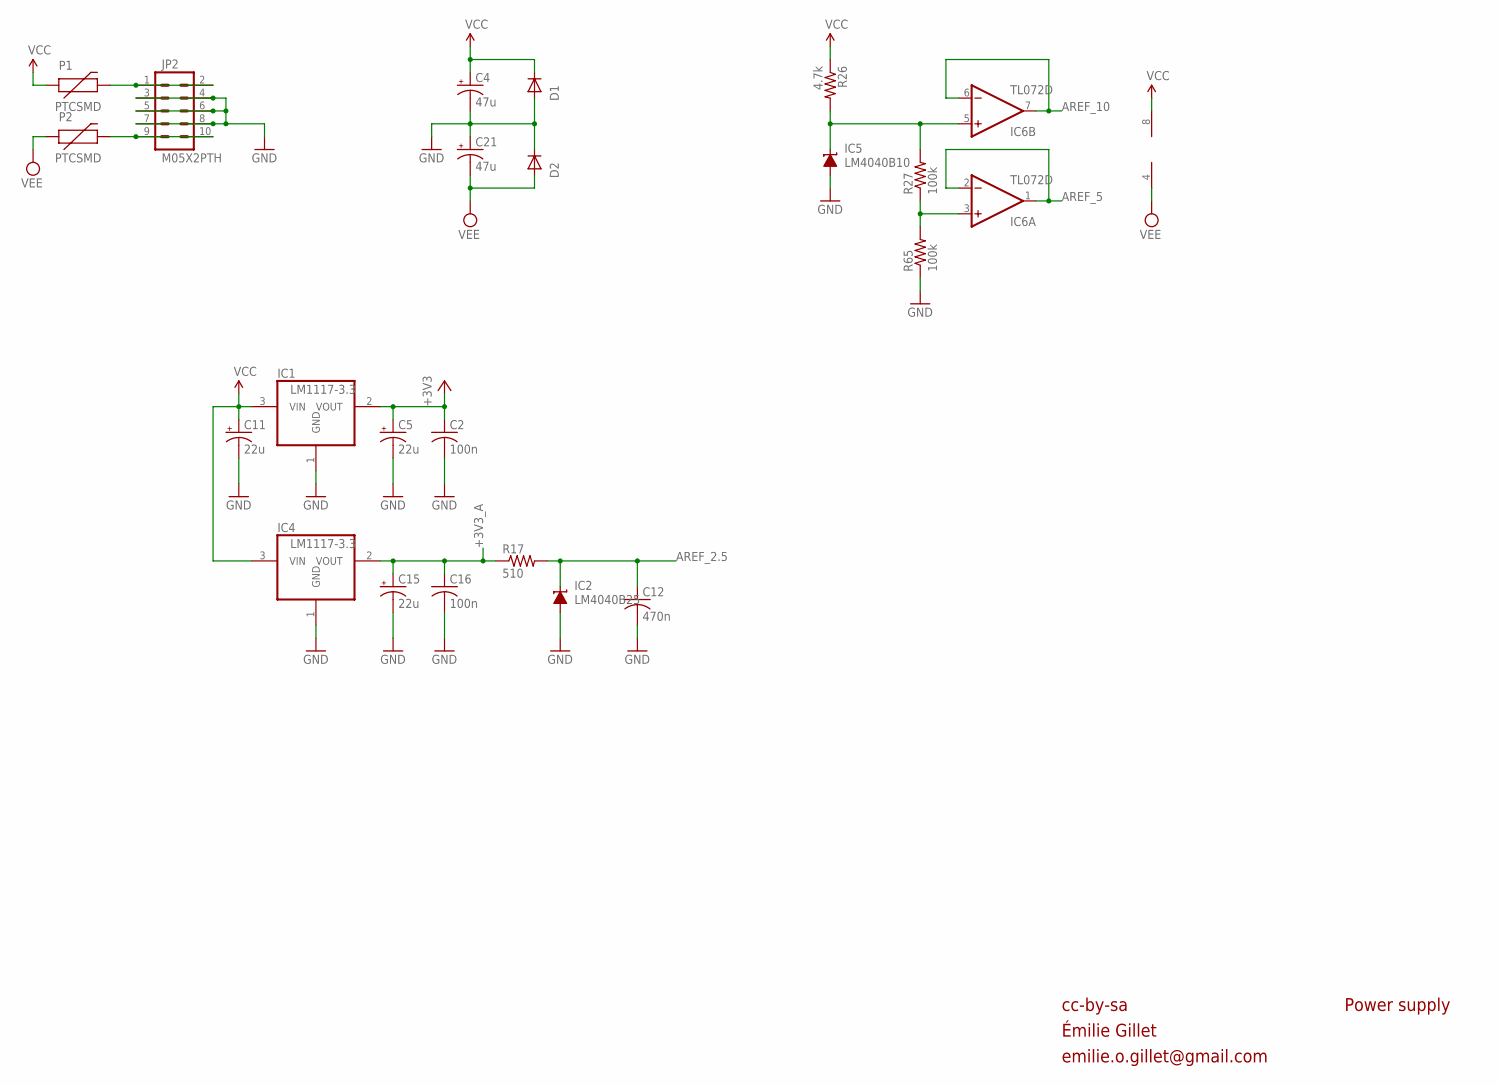
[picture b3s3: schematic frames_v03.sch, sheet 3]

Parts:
C2, C16: 100n; C0603
C4, C21: 47u; PANASONIC_D
C5, C11, C15: 22u; PANASONIC_C
C12: 470n; C0603
D1, D2: 1N5819HW; SOD123
IC1, IC4: LM1117-3.3; SOT223
IC2: LM4040B25; DBZ_R-PDSO-G3
IC5: LM4040B10; DBZ_R-PDSO-G3
IC6: TL072D; SO08
JP2: M05X2PTH; AVR_ICSP
P1, P2: PTCSMD; PTC-1206
R17: 510; R0603
R26: 4.7k; R0603
R27, R65: 100k; R0603

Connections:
+3V3: C2.1, C5.+, IC1.2 (VOUT); also elsewhere on the board
+3V3_A: C15.+, C16.1, IC4.2 (VOUT), R17.1; also elsewhere on the board
AREF_2.5: C12.1, IC2.1 (C), R17.2; also elsewhere on the board
AREF_5: IC6.1 (OUT), IC6.2 (-IN); also elsewhere on the board
AREF_10: IC6.6 (-IN), IC6.7 (OUT); also elsewhere on the board
AREF_10_0: IC5.1 (C), IC6.5 (+IN), R26.2, R27.2
GND: C2.2, C4.-, C5.-, C11.-, C12.2, C15.-, C16.2, C21.+, D1.A, D2.C, IC1.1 (GND), IC2.2 (A), IC4.1 (GND), IC5.2 (A), JP2.3, JP2.4, JP2.5, JP2.6, JP2.7, JP2.8, R65.1; also elsewhere on the board
unnamed: IC6.3 (+IN), R27.1, R65.2
unnamed: JP2.1, JP2.2, P1.2
unnamed: JP2.9, JP2.10, P2.2
VCC: C4.+, C11.+, D1.C, IC1.3 (VIN), IC4.3 (VIN), IC6.8 (V+), P1.1, R26.1; also elsewhere on the board
VEE: C21.-, D2.A, IC6.4 (V-), P2.1; also elsewhere on the board

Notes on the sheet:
cc-by-sa
Power supply
Émilie Gillet
emilie.o.gillet@gmail.com
